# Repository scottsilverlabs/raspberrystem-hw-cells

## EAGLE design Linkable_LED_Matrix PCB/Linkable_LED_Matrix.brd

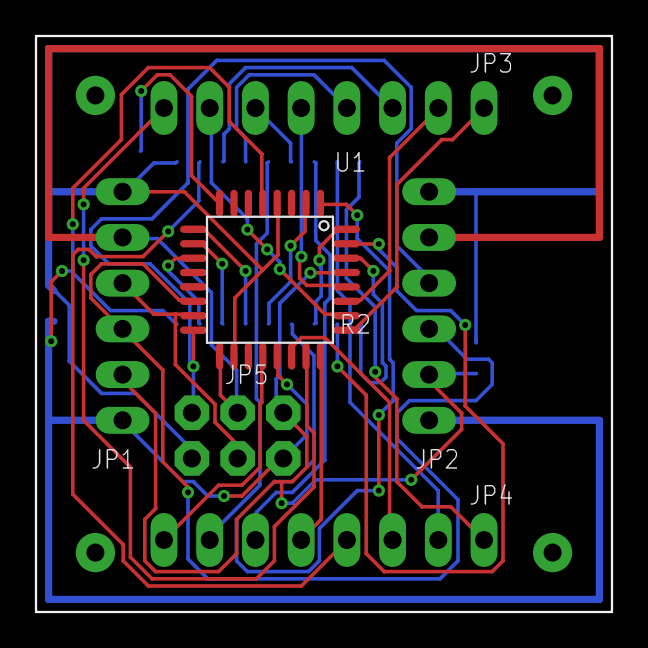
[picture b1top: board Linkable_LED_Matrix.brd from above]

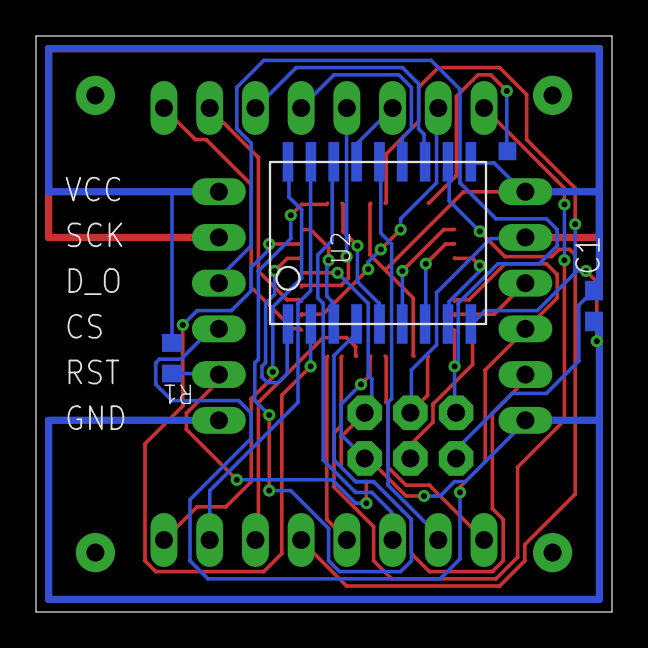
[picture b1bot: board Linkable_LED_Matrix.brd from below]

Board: 2 copper layers, 32.0 x 32.0 mm, 9 parts (5 on the bottom side), 32 nets.

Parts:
C1: 1uF; C0603
R1: R0603
U$1: ATTINY48
U$2: ULN2803AFWG
U$3: 8X8_LED_MATRIX
U$5: 1X1MM_PAD
U$6, U$7: DIP1X6MALE
U$9: DIP2X3MALE

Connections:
COL0: U$1.PD0, U$2.I1
COL1: U$1.PD1, U$2.I2
COL2: U$1.PD2, U$2.I3
COL3: U$1.PD3, U$2.I4
COL4: U$1.PD4, U$2.I5
COL5: U$1.PD5, U$2.I6
COL6: U$1.PD6, U$2.I7
COL7: U$1.PD7, U$2.I8
CS: U$1.PB2, U$6.3, U$7.3
GND: C1.2, U$1.AGND, U$1.GND, U$2.GND, U$6.1, U$7.1, U$9.GND
MISO: U$1.PB4, U$7.4, U$9.MISO
MOSI: U$1.PB3, U$6.4, U$9.MOSI
unnamed: U$2.O1, U$3.COL0
unnamed: U$2.O2, U$3.COL1
unnamed: U$2.O3, U$3.COL2
unnamed: U$2.O4, U$3.COL3
unnamed: U$2.O5, U$3.COL4
unnamed: U$2.O6, U$3.COL5
unnamed: U$2.O7, U$3.COL6
unnamed: U$2.O8, U$3.COL7
unnamed: U$1.PB7, U$5.P$1
RESET: R1.2, U$1.PC6, U$6.2, U$7.2, U$9.RESET
ROW0: U$1.PC7, U$3.ROW0
ROW1: U$1.PA1, U$3.ROW1
ROW2: U$1.PC0, U$3.ROW2
ROW3: U$1.PC1, U$3.ROW3
ROW4: U$1.PC2, U$3.ROW4
ROW5: U$1.PC3, U$3.ROW5
ROW6: U$1.PC4, U$3.ROW6
ROW7: U$1.PC5, U$3.ROW7
SCK: U$1.PB5, U$6.5, U$7.5, U$9.SCK
VCC: C1.1, R1.1, U$1.AVCC, U$1.VCC, U$2.COMMON, U$6.6, U$7.6, U$9.5V
